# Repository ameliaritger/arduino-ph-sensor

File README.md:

# Arduino pH sensor 

## What's in this repository?
This repository contains the scripts and files related to the development of an intertidal Arduino pH sensor.

This repository is maintained by Hofmann Lab graduate student Amelia Ritger (GitHub: [@ameliaritger](https://github.com/ameliaritger)) at the University of California, Santa Barbara in the Department of Ecology, Evolution, & Marine Biology. Please direct any questions or comments about this repository to [Amelia Ritger](mailto:aritger@ucsb.edu).

## How is this repository structured?
```
.
├── documentation/                              # folder containing documentation for building the Arduino data logger for the pH sensor project
│   └── arduinoPHConstructionOperation.docx     # document for building the Arduino data logger
|
├── software/                                   # folder containing software relevant to the Arduino data logger
|   └── arduinoCode/                            # folder containing C++ code to program the Arduino
|      └── CONFIG.h                             # configuration script, to set filename, sampling interval, and sampling start date & time
|      └── SRC.h                                # source script, for useful functions
|      └── arduinoCode.ino                      # main script, to sample from the pH sensor and store the values on the Arduino
|           
|   └── rCode/                                  # folder containing R code to process pH sensor data. Note: currently formatted for project development, not finalized for public application!
|      └── Final_OMEGAS.Rmd                     # Step 3: Apply calibration constants to deployment data
|      └── Final_Tris_Cal.Rmd                   # STEP 2: Calculate calibration constants for the sensor
|      └── Final_deploy_voltages.Rmd            # STEP 4: Plot calibrated sensor data with HOBO logger temperature data
|      └── Final_standardize_data.Rmd           # STEP 1: Standardize Arduino (new design) and Madgetech (old design) data
|
├── media/                                      # folder containing media files for project repo
|
├── draft_files/                                # folder containing all draft project files related to initial testing and development
|
├── README.md
├── .gitignore        
└── ph-sensor-dev.Rproj
```

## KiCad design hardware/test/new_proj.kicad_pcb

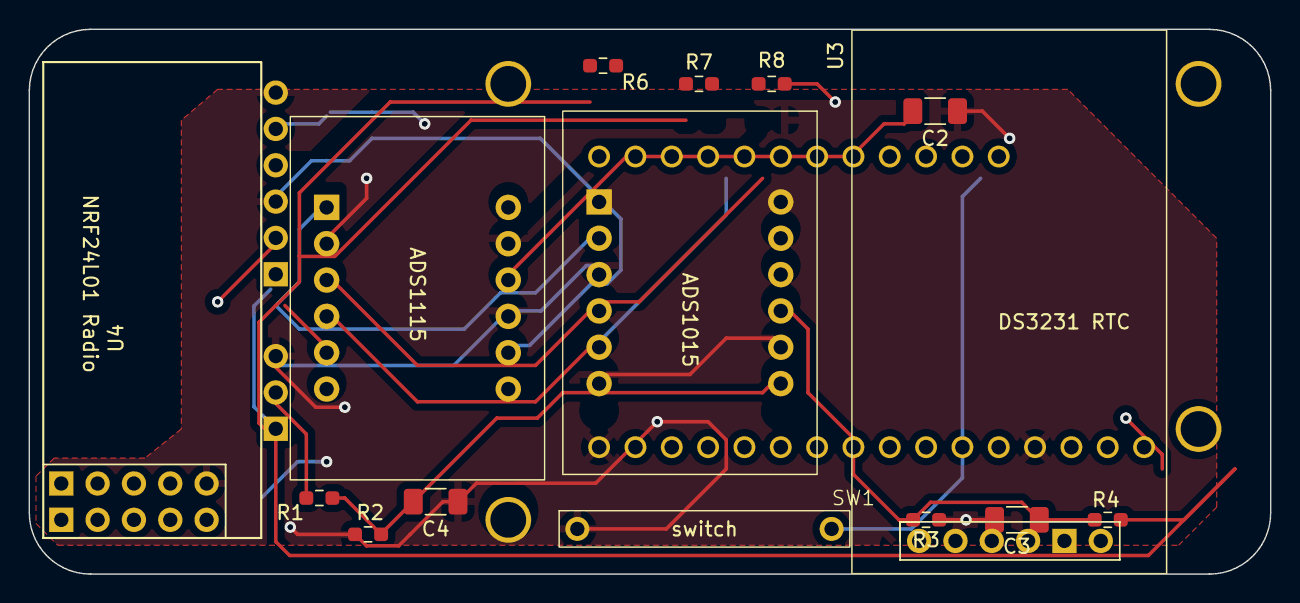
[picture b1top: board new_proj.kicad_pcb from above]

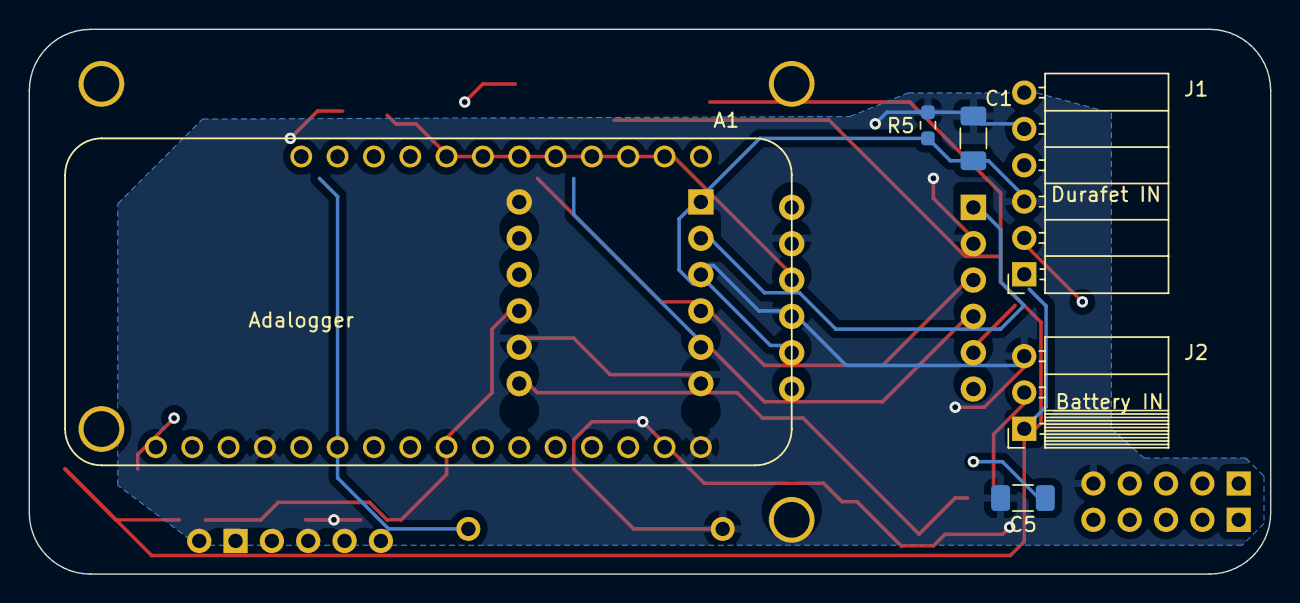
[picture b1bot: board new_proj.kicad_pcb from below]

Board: 2 copper layers, 86.8 x 38.1 mm, 21 parts (6 on the bottom side), 17 nets.

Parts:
A1: Adafruit_Feather_M0_Adalogger; Adalogger_amelia_nomount
C1: 22uF; C_1206_3216Metric_Pad1.33x1.80mm_HandSolder
C2, C3, C4: 100uF; C_1206_3216Metric_Pad1.33x1.80mm_HandSolder
C5: 10uF; C_1206_3216Metric_Pad1.33x1.80mm_HandSolder
J1: Conn_01x06_Pin; PinSocket_1x06_P2.54mm_Horizontal
J2: Conn_01x03_Pin; PinSocket_1x03_P2.54mm_Horizontal
R1, R4, R5, R6, R7: 1M; R_0603_1608Metric_Pad0.98x0.95mm_HandSolder
R2, R3: 10k; R_0603_1608Metric_Pad0.98x0.95mm_HandSolder
R8: 15k; R_0603_1608Metric_Pad0.98x0.95mm_HandSolder
SW1: SW_Reed; REED_amelia
U1, U2: ADS_Ritger; ADC_amelia_nomount
U3: DS3231MZ; DS3231RTC_amelia
U4: NRF24L01_Breakout; NRF24L01Module

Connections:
+BATT: A1.2 (3V3), C5.1, J1.1, J2.1, R4.1, R6.1, R7.2, U1.1 (VDD), U1.5 (ADDR), U2.1 (VDD), U3.2 (VCC), U4.1 (VCC)
-BATT: J1.2, J2.2, R1.1
GND: A1.4 (GND), A1.16 (GND), C1.2, C2.2, C3.2, C4.2, C5.2, J1.3, J1.6, J2.3, R2.2, R3.2, R5.2, R8.1, SW1.1, U1.2 (GND), U1.8 (AIN3), U1.10 (AIN1), U2.2 (GND), U2.5 (ADDR), U2.10 (AIN1), U3.1 (GND), U4.9 (GND)
MISO: A1.13 (MISO/D22), U4.8 (MISO)
MOSI: A1.12 (MOSI/D23), U4.5 (MOSI)
unnamed: A1.19 (D5), U3.5 (~INT/SQW)
unnamed: A1.20 (D6), U4.4 (CE)
unnamed: A1.22 (D10), U4.3 (~CSN)
unnamed: A1.24 (D12), SW1.2
unnamed: R7.1, R8.2
unnamed: C4.1, R1.2, R2.1, U2.11 (AIN0)
unnamed: C3.1, R3.1, R4.2, U2.9 (AIN2)
RTH_High: C2.1, J1.5, R6.2, U1.9 (AIN2)
SCK: A1.11 (SCK/D24), U4.6 (SCK)
SCL: A1.18 (SCL/D21), U1.3 (SCL), U2.3 (SCL), U3.4 (SCL)
SDA: A1.17 (SDA/D20), U1.4 (SDA), U2.4 (SDA), U3.3 (SDA)
pH: C1.1, J1.4, R5.1, U1.11 (AIN0)

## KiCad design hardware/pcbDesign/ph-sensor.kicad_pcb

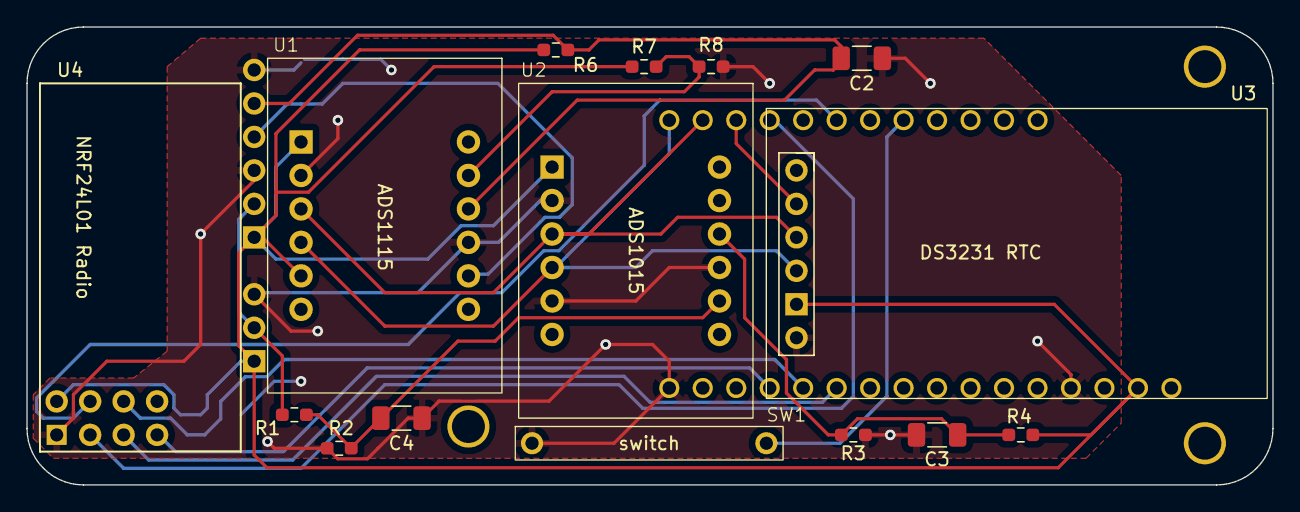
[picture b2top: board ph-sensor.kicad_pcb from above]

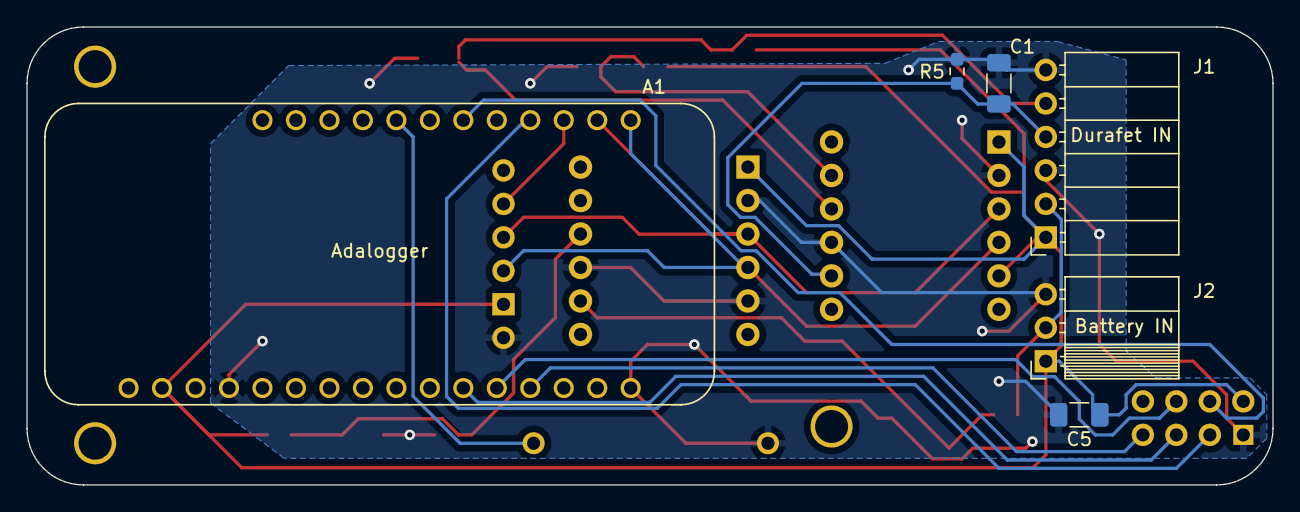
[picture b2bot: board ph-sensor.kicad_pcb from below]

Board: 2 copper layers, 94.5 x 34.7 mm, 21 parts (6 on the bottom side), 17 nets.

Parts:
A1: Adafruit_Feather_M0_Adalogger; Adalogger_amelia_nomount
C1, C2, C3, C4, C5: C; C_1206_3216Metric_Pad1.33x1.80mm_HandSolder
J1: Conn_01x06_Pin; PinSocket_1x06_P2.54mm_Horizontal
J2: Conn_01x03_Pin; PinSocket_1x03_P2.54mm_Horizontal
R1, R2, R3, R4, R5, R6, R7, R8: R_US; R_0603_1608Metric_Pad0.98x0.95mm_HandSolder
SW1: SW_Reed; REED_amelia
U1, U2: ADS_Ritger; ADC_amelia_nomount
U3: DS3231MZ; DS3231RTC_amelia
U4: NRF24L01_Breakout; NRF24L01Module

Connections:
+BATT: A1.2 (3V3), C5.1, J1.1, J2.1, R4.1, R6.1, R7.2, U1.1 (VDD), U1.5 (ADDR), U2.1 (VDD), U3.5 (VCC), U4.2 (VCC)
-BATT: J1.2, J2.2, R1.1
GND: A1.4 (GND), A1.16 (GND), C1.2, C2.2, C3.2, C4.2, C5.2, J1.3, J1.6, J2.3, R2.2, R3.2, R5.2, R8.1, SW1.1, U1.2 (GND), U1.10 (AIN1), U2.2 (GND), U2.5 (ADDR), U2.10 (AIN1), U3.6 (GND), U4.1 (GND)
MISO: A1.13 (MISO/D22), U4.7 (MISO)
MOSI: A1.12 (MOSI/D23), U4.6 (MOSI)
unnamed: A1.19 (D5), U3.2 (~INT/SQW)
unnamed: A1.20 (D6), U4.3 (CE)
unnamed: A1.22 (D10), U4.4 (~CSN)
unnamed: A1.24 (D12), SW1.2
unnamed: R7.1, R8.2, U1.8 (AIN3)
unnamed: C4.1, R1.2, R2.1, U2.11 (AIN0)
unnamed: C3.1, R3.1, R4.2, U2.9 (AIN2)
RTH_High: C2.1, J1.5, R6.2, U1.9 (AIN2)
SCK: A1.11 (SCK/D24), U4.5 (SCK)
SCL: A1.18 (SCL/D21), U1.3 (SCL), U2.3 (SCL), U3.3 (SCL)
SDA: A1.17 (SDA/D20), U1.4 (SDA), U2.4 (SDA), U3.4 (SDA)
pH: C1.1, J1.4, R5.1, U1.11 (AIN0)

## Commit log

2022-12-16 move over files to new repo
2022-12-16 append identifying information, select single calibration value
2022-12-16 append identifying information
2022-12-16 compare arduino tolerance values
2022-12-16 rename cols for later df merge
2022-12-16 add hobo temp data, plot it all up
2022-12-17 testing week code
2022-12-17 fix arrange and slice order issue.
2022-12-17 first push? merge to compare deployment data.
2022-12-17 look at difference between hobo and loggers, and then difference between loggers
2022-12-17 fix filter by date_time.
2022-12-17 fix filter by date_time, compare HOBO and loggers.
2022-12-17 run temperature correction date to plot.
2022-12-17 specify which logger is taking reading.
2022-12-17 add geom_ribbon to plot deployment data after correction.
2022-12-17 add geom_ribbon to plot tris calibration data comparison.
2022-12-17 apply correction equation to arduino data.
2022-12-17 test correction data when comparing loggers.
2022-12-19 visualization and graphing deployment data - pre-subset for correct date/time
2022-12-19 plot data pre-subset with correct date/time and plot sensor swap data.
2022-12-19 raw data, cleaned for correct start/end date and time.
2022-12-19 move old R scripts to draft.
2022-12-20 plot differences between swapped sensors, clean up lag data to get accurate numbers.
2022-12-20 "real" scripts - use these moving forward!
2022-12-20 Annotate and add arrows around Mean.
2022-12-20 Lag field deployment data to get sensor measurement differences.
2022-12-20 double check sensors are in order before lag().
2023-03-01 add LICENSE
2023-03-25 new figures as of march 23
2023-03-25 apply calibration coefficients (using HOBO temp data) to deployment and calibration data
2023-03-25 compare madgetech/arduino reads during sensor swap
2023-03-25 compare reads against HOBO temperature data to calculate correction coefficients for each sensor
2023-03-25 calculate temperature correction coefficients for each collected date/temperature
2023-03-25 apply HOBO temperature correction coefficients to deployment data
2023-03-25 dec 2022 deployment figures
2023-03-25 raw data for sensor swap
2023-03-25 Dec 2022 sensor swap prelim visualization figures
2023-03-25 Dec 2022 initial comparison figures
2023-03-25 Dec 2022 correction calilbration figures
2023-03-25 HOBO temperature data from Dec 2022 sensor tests
2023-03-25 Dec 2022 tables for HOBO temperature correction plotting
2023-03-25 hobo correction figures from Mar 2023 re-analysis
2023-03-25 add all calibrated data
2023-03-25 Dec 2022 raw sensor swap figures
2023-03-25 march 2023 re-analysis sensor swap figure tests
2023-03-25 make note of where swapped correction coefficients come from
2023-03-27 upload from Windows field laptop.
2023-03-27 Add Read/Write ADC inputs, successful compile with printing timestamp to SD card.
2023-03-27 Successful print timestamp callback to SD card; Change serial and df print to Streaming format
2023-03-31 for testing.
2023-04-01 add if/else statement to loop(), add sleep mode, remove ADC inputs.
2023-04-02 Code that works! Oversamples mean, min, and max successfully.
2023-04-02 Print to SD card.
2023-04-03 add sd/variance calculation.
2023-04-03 set gain values appropriately.
2023-04-03 add SD calculation to SD card write.
2023-04-03 Justify oversampling and oversampling rate
2023-04-03 Plot up "noise" figure for oversampled vs not oversampled data.
2023-04-04 instead of oversampling and mean/min/max, just collect all raw oversample values all at once for processing later.
2023-04-04 add calculate SD.
2023-04-04 SIMPLIFY to only oversample one pin to test current draw for each oversampling event.
2023-04-08 first half testing arduino/madgetech in lab
2023-04-08 add lab data from 4.8
2023-04-10 add ice cold data.
2023-04-10 oversample comparison data.
2023-04-10 add lab data madgetech 4.10.
2023-04-11 edit for new data collected 4.9 with simultaneous 64/256x sampling.
2023-04-11 make nice plot of 4.9 oversampling data.
2023-04-12 4.11 swap data.
2023-04-13 add arduino day 4.12 data
2023-05-22 upload all arduino c code
2023-05-22 upload first pass cleaned up Arduino code
2023-05-22 move specific R files to software folder
2023-05-22 delete?
2023-05-22 move files over to draft folder
2023-05-22 start draft construction and operation file.
2023-05-22 update ReadMe (test file location).
2023-05-22 take 2 test folder location.
2023-05-23 documentation pending.
2023-06-05 Add folder structure.
2023-06-06 add image to readme.
2023-06-06 add media folder.
2023-06-06 clean up folder structure.
2023-06-06 change comment formatting.
2023-06-06 add D1 documentation.
2023-08-16 ignore draft_files/.
2023-08-16 gitignore draft_files.
2023-08-16 gitignore draft_files/.
2023-08-16 rename draft_files/ to temp/ and gitignore.
2023-09-25 Use SdFat library to put SD card to sleep.
2023-09-25 Use EKMallon modified RTC with Adalogger/DS3232RTC
2023-09-26 it "works" but still consuming a lot of power
2023-10-11 tx/rx functioning code plus reed switch plus serial communication for blink
2023-10-11 create BlinkWithoutDelay function
2023-10-11 Send data regardless of new Serial input, add blink without delay function
2023-10-13 Add code drafts (since wireless added)
2023-10-13 new working code for Adalogger and Pro Mini with NRF24L01
2023-11-03 add first draft KiCAD files
2023-11-28 update README repo structure descriptions
2024-01-13 V1 JLCPCB design
2024-01-22 update pcb schematic/design
2024-01-26 add comparison data and write up code
2024-01-26 compare 36 hours data, adjusted SeaFET with Arduino design
2024-01-26 include temps
2024-01-26 adjust for number of rows removed
2024-01-26 Check serial failure
2024-01-26 test again
2024-01-26 packet loss 1 month data
2024-01-27 3 month packet loss
2024-01-27 2 months data
2024-01-27 1 month data
2024-01-27 32 byte packets
2024-01-27 Generate fake data to measure transmission packet loss rate
2024-01-28 add adc reset code
2024-01-29 Add functional code Jan 28 2024 incl serial comms
2024-01-29 Add code drafts since jan 28 2024
2024-01-29 View power consumption with V2 code/hardware
2024-01-31 overwrite in-between periods with sleep current, add triangles for reed switch activation
2025-04-06 Edit to re-create deployment figure for dissertation
2025-04-06 update sensor swap figures for publication in dissertation
2025-04-06 update current consumption fig for dissertation
